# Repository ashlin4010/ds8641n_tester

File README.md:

# DS8641N Tester
A simple tester for DS8641N chips.

## Usage ##
 1. Plug it into 5 volt power centre positive power.
 2. Install chip
 3. Press Buttons

## Bill of materials ##

| Quantity | Part | Link |
|:---:|:---:|:---:|
| 8 | 1K Resistor |  |
| 4 | 10K Resistor |  |
| 6 | Push Button | https://www.digikey.co.nz/en/products/detail/same-sky-formerly-cui-devices/TS02-66-70-BK-160-LCR-D/15634243 |
| 1 | Barrel Jack | https://www.digikey.co.nz/en/products/detail/same-sky-formerly-cui-devices/PJ-037A/1644545 |
| 1 | DIP-16 ZIF Socket | https://www.aliexpress.com/item/1005007048855354.html |
| 1 | 74HCT541 | https://www.digikey.co.nz/en/products/detail/texas-instruments/SN74HCT541N/277265 |
| 1 | 390ohm Bussed | https://www.digikey.co.nz/en/products/detail/bourns-inc/4606X-101-391LF/1088986 |
| 1 | 180ohm Bussed | https://www.digikey.co.nz/en/products/detail/bourns-inc/4606X-101-181LF/1088969 |
| 8 | 3mm LED RED |  |

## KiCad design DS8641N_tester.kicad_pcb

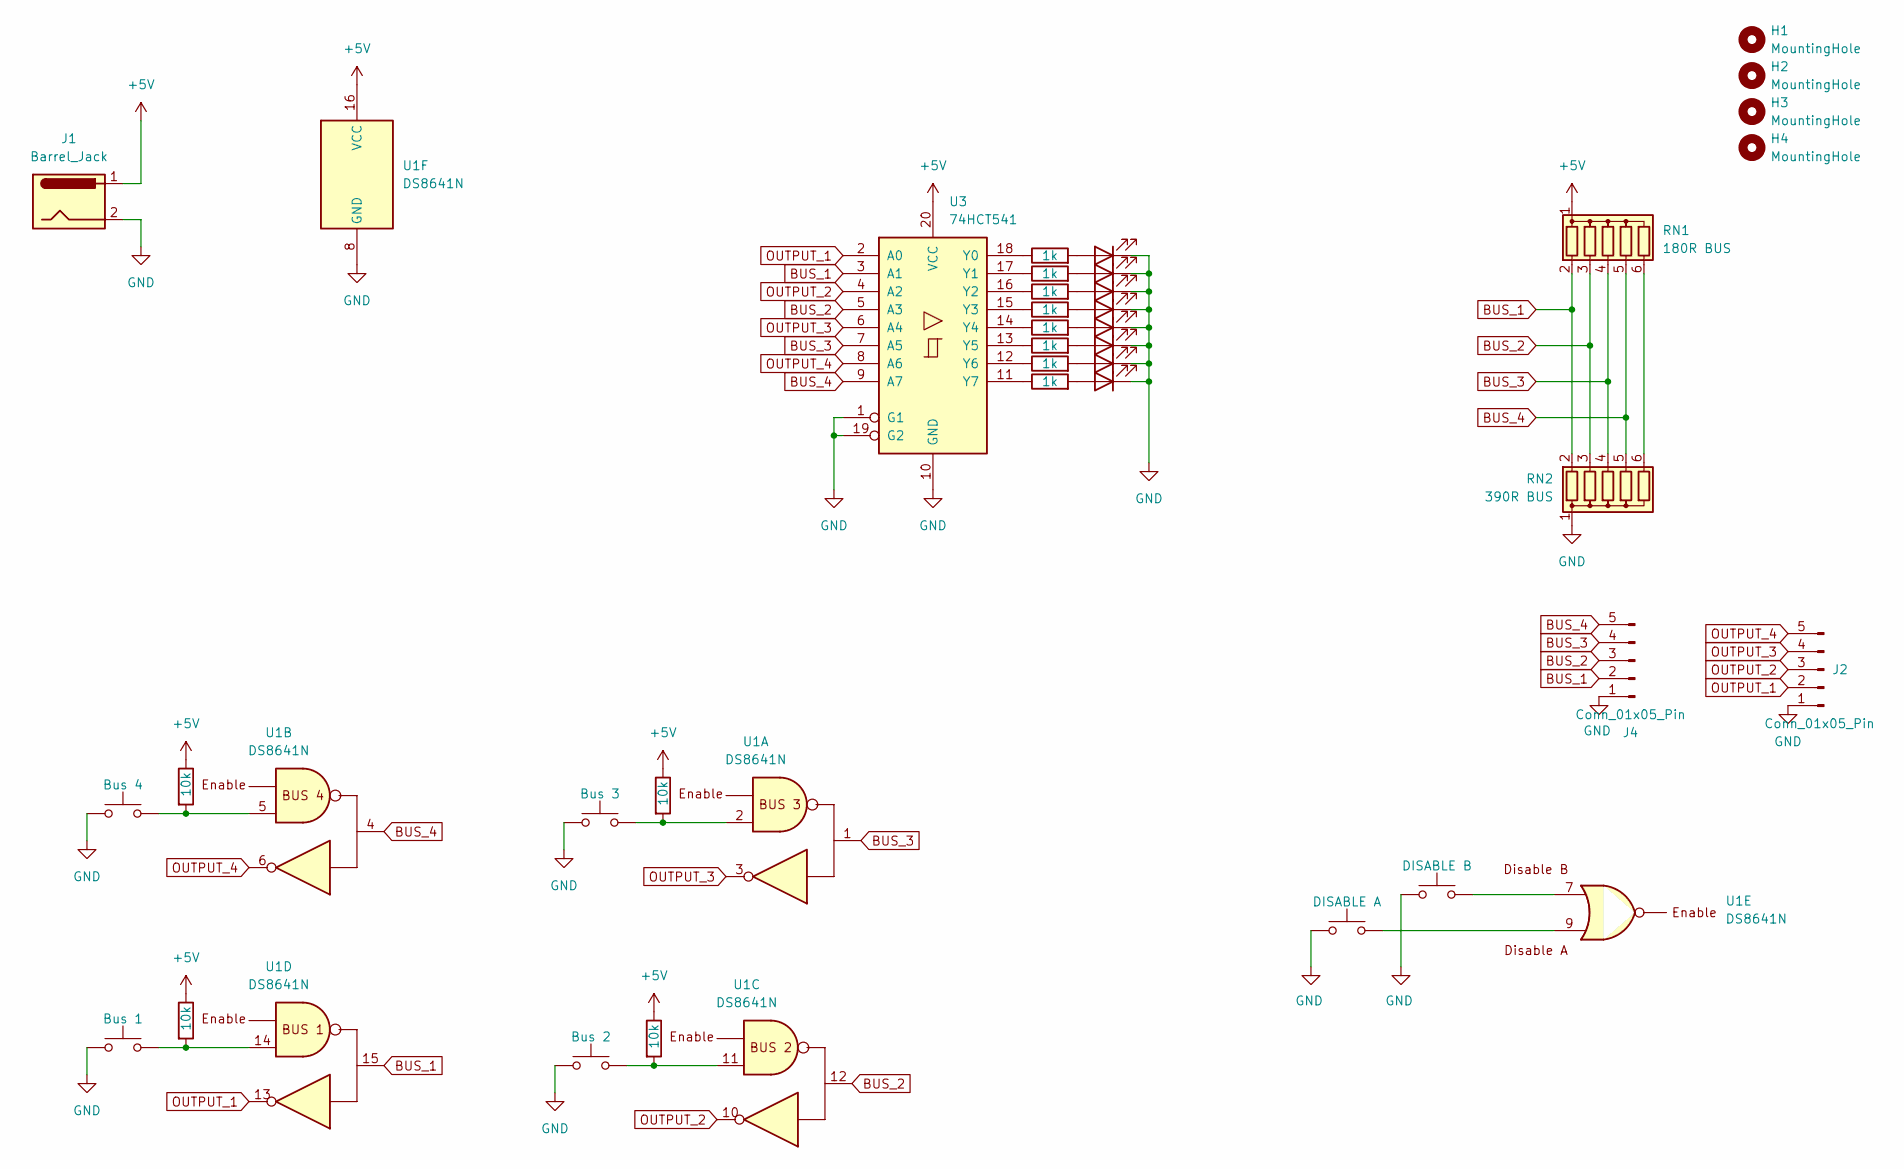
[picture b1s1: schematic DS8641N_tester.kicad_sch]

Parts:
D2, D3, D4, D5, D6, D7, D8, D9: LED; LED_D3.0mm
H1, H2, H3, H4: MountingHole; MountingHole_3.2mm_M3
J1: Barrel_Jack; BarrelJack_GCT_DCJ200-10-A_Horizontal
J2, J4: Conn_01x05_Pin; PinHeader_1x05_P2.54mm_Vertical
R2, R3, R4, R5: 10k; R_Axial_DIN0204_L3.6mm_D1.6mm_P7.62mm_Horizontal
R8, R9, R10, R11, R12, R13, R14, R15: 1k; R_Axial_DIN0204_L3.6mm_D1.6mm_P7.62mm_Horizontal
RN1: 180R BUS; R_Array_SIP6
RN2: 390R BUS; R_Array_SIP6
SW1: Bus 1; SW_PUSH_6mm_H4.3mm
SW2: Bus 2; SW_PUSH_6mm_H4.3mm
SW3: Bus 3; SW_PUSH_6mm_H4.3mm
SW4: Bus 4; SW_PUSH_6mm_H4.3mm
SW5: DISABLE A; SW_PUSH_6mm_H4.3mm
SW6: DISABLE B; SW_PUSH_6mm_H4.3mm
U1: DS8641N; DIP_Socket-16_W4.3_W5.08_W7.62_W10.16_W10.9_3M_216-3340-00-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
U3: 74HCT541; DIP-20_W7.62mm

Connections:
+5V: J1.1, R2.1, R3.1, R4.1, R5.1, RN1.1 (common), U1.16 (VCC), U3.20 (VCC)
BUS_1: J4.2, RN1.2 (R1), RN2.2 (R1), U1.15, U3.3 (A1)
BUS_2: J4.3, RN1.3 (R2), RN2.3 (R2), U1.12, U3.5 (A3)
BUS_3: J4.4, RN1.4 (R3), RN2.4 (R3), U1.1, U3.7 (A5)
BUS_4: J4.5, RN1.5 (R4), RN2.5 (R4), U1.4, U3.9 (A7)
GND: D2.1 (K), D3.1 (K), D4.1 (K), D5.1 (K), D6.1 (K), D7.1 (K), D8.1 (K), D9.1 (K), J1.2, J2.1, J4.1, RN2.1 (common), SW1.1, SW2.1, SW3.1, SW4.1, SW5.1, SW6.1, U1.8 (GND), U3.1 (G1), U3.10 (GND), U3.19 (G2)
unnamed: D2.2 (A), R8.2
unnamed: D3.2 (A), R9.2
unnamed: D4.2 (A), R10.2
unnamed: D5.2 (A), R11.2
unnamed: D6.2 (A), R12.2
unnamed: D7.2 (A), R13.2
unnamed: D8.2 (A), R14.2
unnamed: D9.2 (A), R15.2
unnamed: R2.2, SW1.2, U1.14
unnamed: R3.2, SW2.2, U1.11
unnamed: R4.2, SW3.2, U1.2
unnamed: R5.2, SW4.2, U1.5
unnamed: RN1.6 (R5), RN2.6 (R5)
unnamed: SW5.2, U1.9
unnamed: SW6.2, U1.7
unnamed: R8.1, U3.18 (Y0)
unnamed: R9.1, U3.17 (Y1)
unnamed: R10.1, U3.16 (Y2)
unnamed: R11.1, U3.15 (Y3)
unnamed: R12.1, U3.14 (Y4)
unnamed: R13.1, U3.13 (Y5)
unnamed: R14.1, U3.12 (Y6)
unnamed: R15.1, U3.11 (Y7)
OUTPUT_1: J2.2, U1.13, U3.2 (A0)
OUTPUT_2: J2.3, U1.10, U3.4 (A2)
OUTPUT_3: J2.4, U1.3, U3.6 (A4)
OUTPUT_4: J2.5, U1.6, U3.8 (A6)

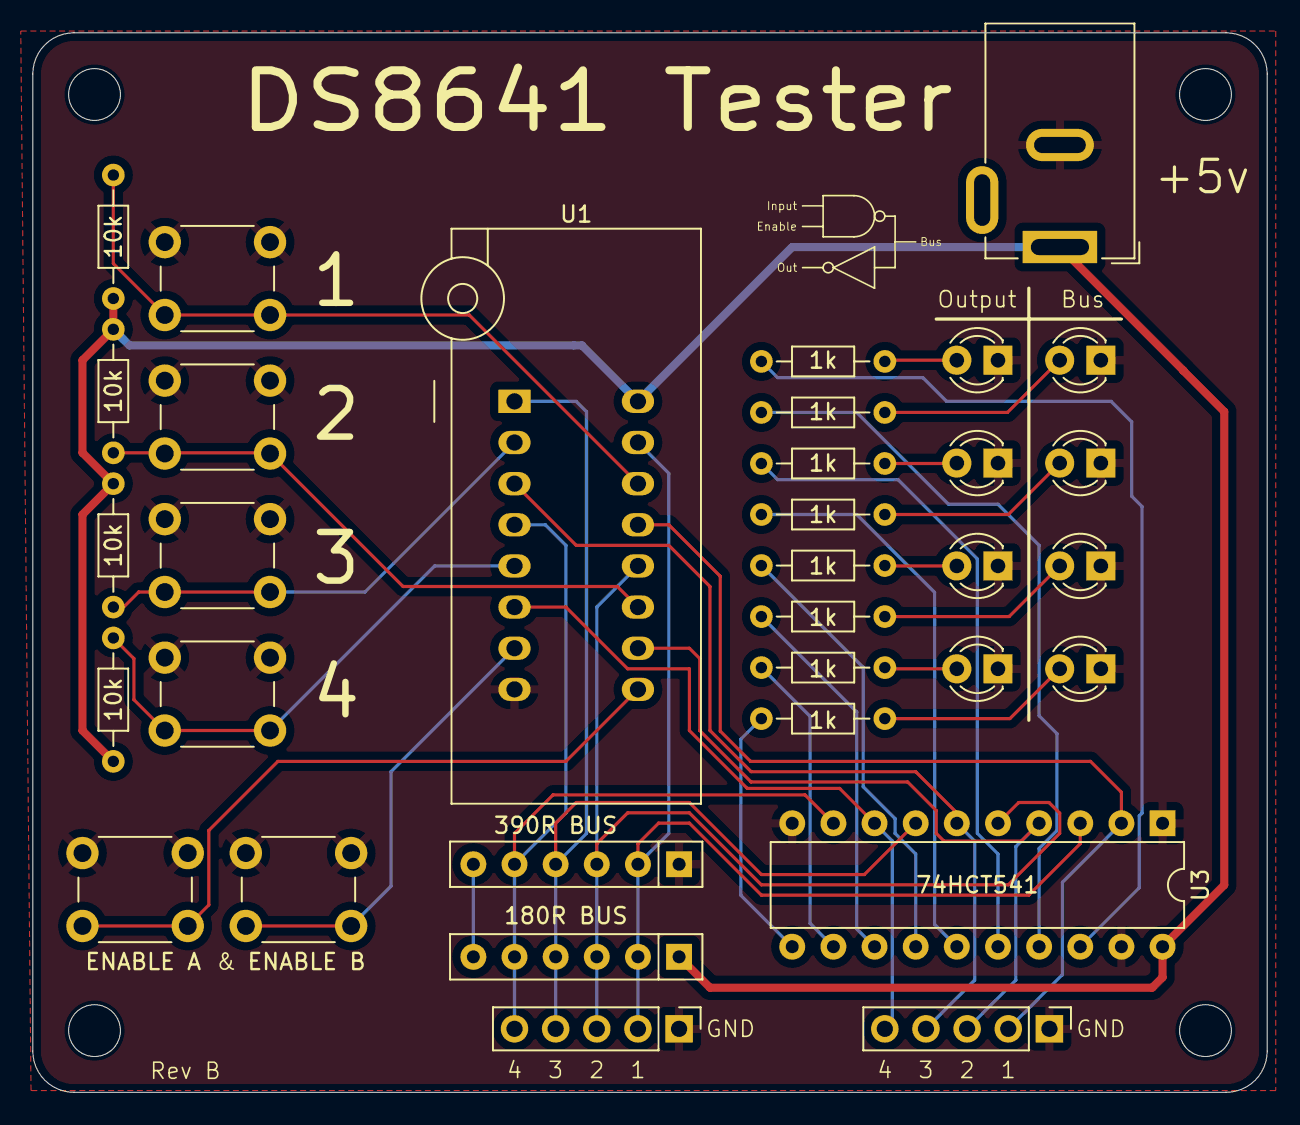
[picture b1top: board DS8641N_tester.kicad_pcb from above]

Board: 2 copper layers, 76.2 x 65.4 mm, 37 parts (0 on the bottom side), 33 nets.

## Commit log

2024-11-19 Added PCB files
2024-12-06 Added image and small fix
